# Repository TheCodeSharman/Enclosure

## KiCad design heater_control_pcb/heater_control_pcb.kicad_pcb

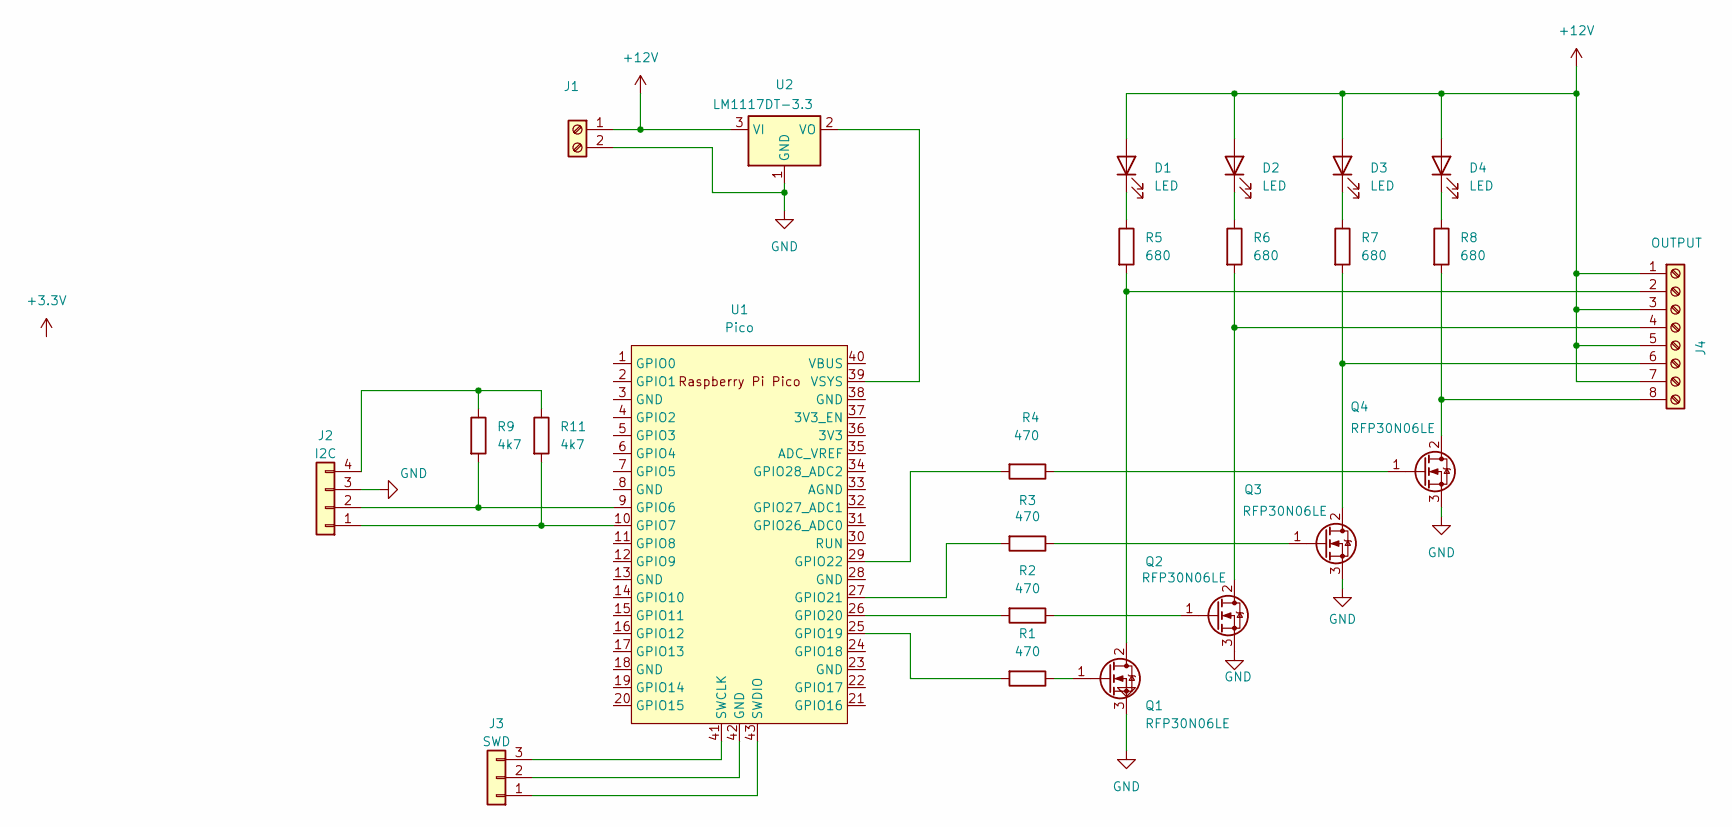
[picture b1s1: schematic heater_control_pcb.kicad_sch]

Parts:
D1, D2, D3, D4: LED; LED_D5.0mm
J1: TerminalBlock_Phoenix_PT-1,5-2-5.0-H_1x02_P5.00mm_Horizontal
J2: I2C; JST_SH_SM04B-SRSS-TB_1x04-1MP_P1.00mm_Horizontal
J3: SWD; PinHeader_1x03_P2.00mm_Vertical
J4: OUTPUT; TerminalBlock_Phoenix_PT-1,5-8-5.0-H_1x08_P5.00mm_Horizontal
Q1, Q2, Q3, Q4: RFP30N06LE; TO-220-3_Vertical
R1, R2, R3, R4: 470; R_Axial_DIN0204_L3.6mm_D1.6mm_P5.08mm_Horizontal
R5, R6, R7, R8: 680; R_Axial_DIN0204_L3.6mm_D1.6mm_P5.08mm_Horizontal
R9, R11: 4k7; R_Axial_DIN0204_L3.6mm_D1.6mm_P5.08mm_Horizontal
U1: Pico; RPi_Pico_SMD_TH
U2: LM1117DT-3.3; TO-252-3_TabPin2

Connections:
+12V: D1.2 (A), D2.2 (A), D3.2 (A), D4.2 (A), J1.1, J4.1, J4.3, J4.5, J4.7, U2.3 (VI)
GND: J1.2, J2.3, Q1.3 (S), Q2.3 (S), Q3.3 (S), Q4.3 (S), U2.1 (GND)
unnamed: D1.1 (K), R5.1
unnamed: D2.1 (K), R6.1
unnamed: D3.1 (K), R7.1
unnamed: D4.1 (K), R8.1
unnamed: J2.1, R11.2, U1.10 (GPIO7)
unnamed: J2.2, R9.2, U1.9 (GPIO6)
unnamed: J2.4, R9.1, R11.1
unnamed: J3.1, U1.43 (SWDIO)
unnamed: J3.2, U1.42 (GND)
unnamed: J3.3, U1.41 (SWCLK)
unnamed: J4.2, Q1.2 (D), R5.2
unnamed: J4.4, Q2.2 (D), R6.2
unnamed: J4.6, Q3.2 (D), R7.2
unnamed: J4.8, Q4.2 (D), R8.2
unnamed: Q1.1 (G), R1.1
unnamed: Q2.1 (G), R2.1
unnamed: Q3.1 (G), R3.1
unnamed: Q4.1 (G), R4.1
unnamed: R1.2, U1.25 (GPIO19)
unnamed: R2.2, U1.26 (GPIO20)
unnamed: R3.2, U1.27 (GPIO21)
unnamed: R4.2, U1.29 (GPIO22)
unnamed: U1.39 (VSYS), U2.2 (VO)

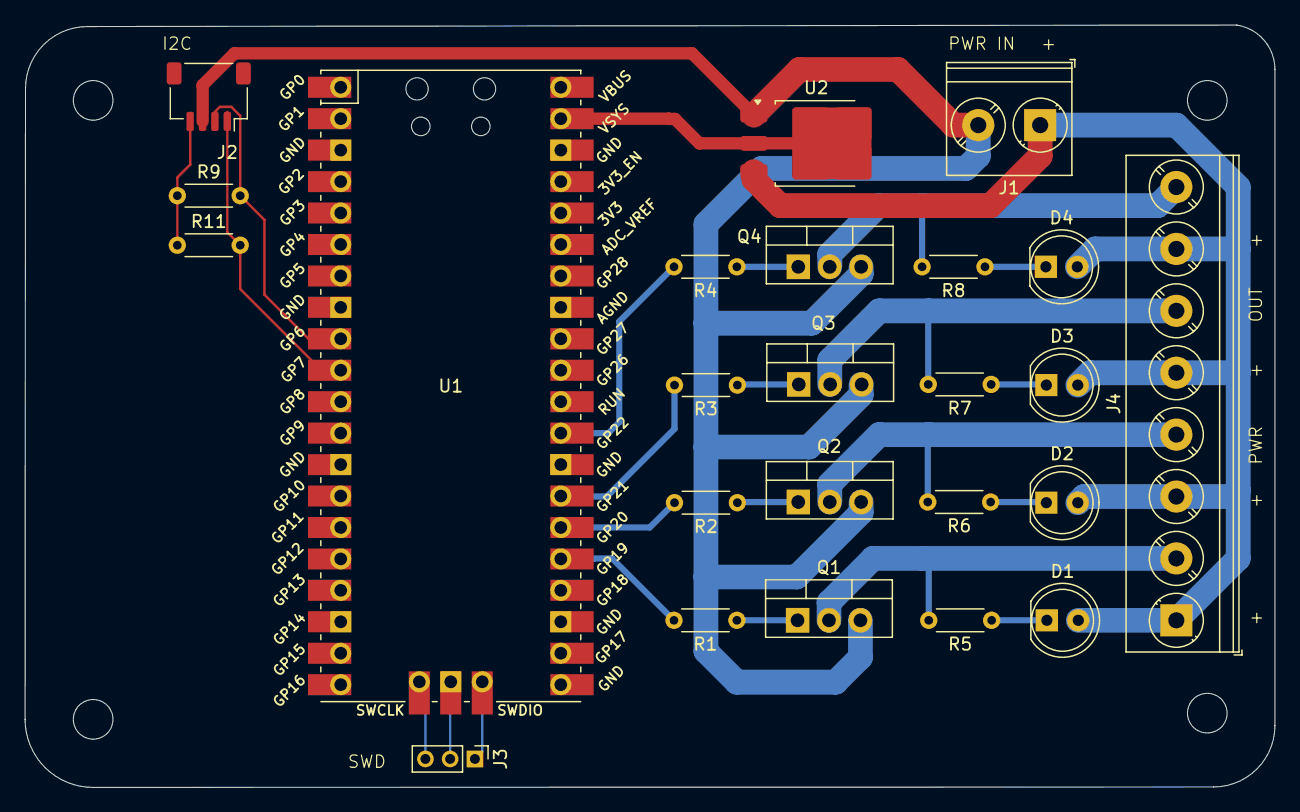
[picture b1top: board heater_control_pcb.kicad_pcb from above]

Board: 2 copper layers, 101.0 x 61.6 mm, 24 parts (0 on the bottom side), 25 nets.

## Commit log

2019-02-17 initial version
2019-02-18 revision 2
2019-02-18 added render() to fix preview glitches
2019-02-18 remove duplicate Corners.scad
2019-02-18 tweaks for a better fit
2019-02-18 add top left back and refactor
2019-02-19 Cleaned up parameters
2019-02-19 refactred code and added a model of the panels
2019-02-19 moved hinges to make doors fit without further cutting
2019-02-24 modify hinge to fit properly within the enclosure
2019-02-24 enclose the door on the bottom
2019-02-24 fill the gap near the hinge post
2019-02-24 add vertical frame modules ;
2019-02-24 added connector tabs inbetween vetical frame segments
2019-03-02 split into separate modules
2019-03-02 factor out views into separate functions and adda working view
2019-03-02 factor out each component into a separate file: this means a component can be worked on easily one at a time
2019-03-02 add outside frame construction functions
2019-03-02 modified tolerances based on test prints
2019-03-02 fix typo
2019-03-02 further tweak to clearances
2019-03-03 add back vertical frame and refactor frame extension
2019-03-03 add exploded view of reset of pieces
2019-03-03 swicth children(0) for children() so that modifiers don't spuriously remove extra children
2019-03-03 fix hinge post to allow hinge to open and adjust clearances yet again
2019-03-03 reduce the clearance around the hinge to reduce the air gaps
2019-09-02 misc updates
2019-09-03 increase thickness of snap on clip
2019-09-03 added top right snap lock
2019-09-03 add back right components
2019-09-03 move gap to top on back to make room for filament guides
2019-09-03 fix exploded view
2019-09-05 tweaks to make parts fit well
2019-09-06 added a make file to allow efficient building of individual parts
2024-07-07 Add initial version of enclosure control Octoprint plugin
2024-07-27 Add modification to fs-cover part
2024-07-28 WIP filament path guide
2024-07-28 Update enclosure files
    Add door frame arms to hinges - its hard to fit on a single plater but
    it is just possible and this hopefully makes the dppr frame les inclined
    to fall apart.
    Also change the thickness of the perspect doors it was too large which
    was probably the main reason the parts kept falling off.
    Also use larger magnets so the doors stay closed.
2024-07-31 Created assembly for enclosure
    Added wall panels, doors, to use as construction
    features for the enclosure parts.
2024-07-31 Update of free cad file
2024-07-31 Tweak hinge offsets to be a little more real
2024-07-31 Specify the wall panel colour
2024-07-31 Add some documentation as amrkdown cells
    Might as well make notes here whilst we g - for future self and
    potentially publication purposes.
2024-07-31 Add some eztar show commands
    By have a show in each cell in makes easier to interactively edit
    that part of the model.
2024-08-04 Updated enclosure files in build123d
    Add the walls and doors to allow building the rest of the design around
    them.
2024-08-04 Added first version of heater control board
2024-08-04 Ignore a bunch of KiCad local files
2024-08-10 Added a test version for the heater firmware
    Just turns on all the MOSFETs.
    The firmwar works but it looks like I wired in the LEDs reverse
    polarity so the circuit can't work doh! (Desoldering is no fun)
2024-08-31 Some WIP i2c bus testing
    Doesn't seem tobe finding the TMP117 - not sure why probably need to
    look at the i2c bus with oscilloscope (or logic analyser)
2024-09-01 Add LM7805 datasheet
2024-09-01 Operational i2c It was bad soldering - the SDA line wasn't connected.
2024-09-01 Update schematics to match prototype
    - Added some signal diodes to act as power supply protection:
    - On the 3v3 line on the i2c bus, this drops the voltage to 2v8 but this
    seems to be adeqaute for the TMP117.
    - Between the Pico and the LM7805 to prevent backfeeding the regulator
    when the power isn't connected but the USB bus is.
    Used 1n4148 because I have a ton of them - not ideal in terms of
2024-09-14 We need a second i2c bus!
    Multi-master on i2c should in theory work but it looks like the hardware
    and software is pretty much configured to assume one master out of the
    box.
    To avoid the complications the easiet way forward is to add a 2nd i2c
    port which is a slave.
    So we have:
2024-09-14 Use two i2c ports
    Update firmware to support second i2c port
2025-01-09 backup
2025-01-09 Properly constrained base for hinge
    The previous attempt didn't keep the clearance as specified, this
    version whislt more complicated properly keeps everything at the
    specified clearance.
2025-01-10 A much cleaner construction technique
    Previous we did a lot of construction lines and drawing vectors but we
    can make use of a 1D sweep to achieve the same result with much simpler
    code!
2025-01-10 Add units and tidy up comments
2025-01-10 Further tidy up
2025-01-10 Create `InPlaceHinge` class
    Creates a custom part object that encapsulates the creation of the hinge
    part. Also colors the hinge components to make debugging easier.
2025-01-10 Add the sides to the hinge
2025-01-10 Simply code by using Locations
2025-01-18 Improve labelling of parts
2025-01-18 Re-order hinge parts
2025-01-18 First (broken) attempt at gluing parts
    Use tangent lines to create a profile to subtract or cut from the
    the hinge parts.
    This isn't quite right because it is symmetrical and it should instead
    be offset in order to only join the correct side.
2025-01-19 Joint hinge parts together
    This isn't quite right - I think there needs to be clearance between the
    left and right side or else the hinge will print fused together!!
2025-01-27 Minor clean up
    I prefer the attributes with mutiple on one line so the code is more
    compact.
2025-01-27 Extraxt HingeJointSketch
2025-01-27 Cut away clearance for right side of hinge
2025-02-02 Cur away clearnce meterial frpm left hinge
2025-02-02 Add fillets to hinge edges
2025-02-02 Use more robust selection algorithm
    Select by position rather than relying on index.
2025-02-02 Whitespace clean up
2025-02-02 Fix a gliltch on the the hinge edge
2025-02-02 Consolidate gface selection code
2025-02-02 Use consistent naming convention fro sketchs
